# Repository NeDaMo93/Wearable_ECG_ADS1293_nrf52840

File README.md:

# Wearable_ECG_ADS1293_nrf52840
Software for a Functional Demonstrator of a Medical Wearable for ECG and Activity Monitoring with Wireless Communication. With ADS1293, nrf52840, LSM6DSO. Includes an Android App and Python GUI.
# Summary of the research project
This research project aims to design and develop a functional demonstrator of a portable device for long-term Electrocardiogram (ECG) measurements. The proposed device intends to address the need for continuous and non-invasive monitoring of cardiac activity over extended periods, providing valuable insights into the diagnosis and management of cardiovascular conditions.
In addition to enabling long-term Electrocardiogram (ECG) measurements, the developed wearable device will also incorporate advanced sensors to monitor body position, physical activity, and body temperature continuously. This comprehensive approach aims to provide a holistic assessment of the user's physiological status, allowing for a more thorough evaluation of their overall health. 
The primary objective of this project is to create a working prototype that can serve as a foundation for future advancements in the field. The successful development of this device will facilitate subsequent research projects, fostering innovation and further exploration of long-term ECG monitoring technologies at our institution.
Throughout the research process, various aspects, such as hardware design, signal processing algorithms, power efficiency, and user-friendliness, will be carefully considered and optimized to ensure the device's reliability and practicality. Additionally, emphasis will be placed on achieving a cost-effective solution without compromising the quality of data collected.
Ultimately, the successful completion of this project will lay the groundwork for subsequent investigations, encouraging a continuous cycle of research and development in the domain of portable long-term ECG monitoring. The findings and insights gained from this study will contribute significantly to the improvement of cardiac healthcare and enhance the quality of life for individuals with cardiovascular conditions.
# Hardware Architecture
Based on the requirements, the concept architecture and associated functions could be defined by using specific hardware, which is shown in the following figure. For the demonstrator, Nordic's nRF52840 microcontroller acts as the central element, which is available in the form of a developer board from Adafruit Feather. This board has several integrated functions, including push buttons for triggering external events, LEDs for status indication, and an energy-efficient Bluetooth module. A matching SD card module from Adafruit allows local storage of recorded data. The ADS1293 is used as the analog front end for processing ECG signals. The user's activity level and body position are detected with the help of the ST LSM6DSO IMU. Body temperature is measured by using a PT1000 sensor. The Easypack S rechargeable battery system from Varta supplies the necessary energy. Finally, the collected data is transmitted via Bluetooth to a PC and Android smartphone and displayed.

# Software Architecture
The firmware is designed to efficiently handle data acquisition from the ECG and IMU (Inertial Measurement Unit) sensors and transmit the collected data via Bluetooth Low Energy (BLE) while storing it on an SD card. The architecture is implemented using six components, including four separate threads and two interrupt Service Routines (ISRs).

# User Interfaces
## Anrdoid App
The Android application was constructed using the open-source code provided by Nordic for the Android-nRF-Blinky application. 
The Android-nRF-Blinky application, written in Kotlin, serves as an excellent introduction for developers unfamiliar with Bluetooth Low Energy (BLE) and can serve as a template for other projects.
The application uses the Android BLE Library to manage its Bluetooth connections. When the application starts, it scans for nearby BLE devices. Once a device is selected, the application connects to it and discovers its services and characteristics (using the GATT protocol). 

## Python GUI
The Python-based graphical user interface (GUI) connects the ECG device via Bluetooth Low Energy (BLE) and visualizes real-time ECG data. It also displays the patient's activity level, body temperature, heart rate and body posture. The code utilizes PyQt5 for GUI development, Matplotlib for plotting, asyncio for asynchronous tasks, Bleak for BLE communication, and biosppy for ECG signal processing.

# LBS Files
lbs.h and lbs.c must be replaced in your zephyr directory <br>
**lbs.h:**<br>
..\nrf\include\bluetooth\services<br>
**lbs.c:**<br>
..\nrf\subsys\bluetooth\services<br>

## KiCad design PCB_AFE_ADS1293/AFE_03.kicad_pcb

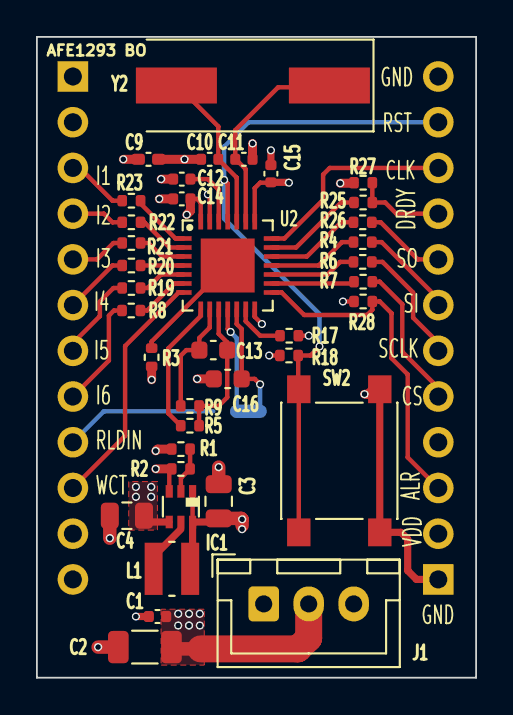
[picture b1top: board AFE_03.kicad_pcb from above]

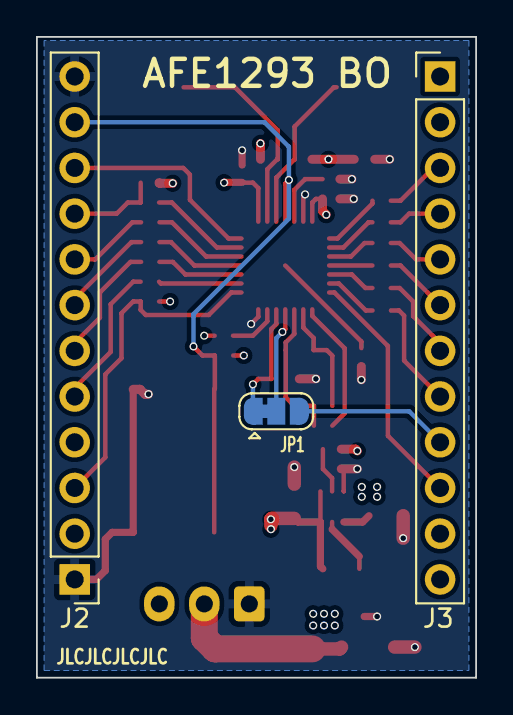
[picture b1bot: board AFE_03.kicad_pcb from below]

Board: 4 copper layers, 24.4 x 35.6 mm, 41 parts (3 on the bottom side), 41 nets.

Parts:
C1, C12, C14, C15: 0.1uF; C_0402_1005Metric
C2: 47uF; C_1206_3216Metric
C3, C4: 10uF; C_0805_2012Metric
C9: 0.1uF; C_0402_1005Metric_Pad0.74x0.62mm_HandSolder
C10, C11: 22pF; C_0402_1005Metric
C13: 1nF; C_0603_1608Metric
C16: 0.1uF; C_0603_1608Metric
IC1: TPS61222DCK; DCK_R-PDSO-G6
J1: Conn_01x03_Socket; JST_XH_B3B-XH-A_1x03_P2.50mm_Vertical
J2, J3: Conn_01x12; PinHeader_1x12_P2.54mm_Vertical
JP1: SolderJumper_3_Open; SolderJumper-3_P1.3mm_Open_RoundedPad1.0x1.5mm
L1: EPL3015-472MLB; IND_EPL3015-472MLB
R1, R17, R18, R27, R28: 1.0M; R_0402_1005Metric
R2: 200k; R_0402_1005Metric
R3, R8, R19, R20, R21, R22, R23: 0; R_0402_1005Metric
R4, R6, R7, R25, R26: 51; R_0402_1005Metric
R5: 10k; R_0402_1005Metric
R9: 10M; R_0402_1005Metric
SW2: SW_SPST; SW_Push_1P1T_NO_6x6mm_H9.5mm
U2: ADS1293CISQ/NOPB; QFN50P500X500X80-29N
Y2: Crystal_Small; Crystal_SMD_HC49-SD

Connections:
ALARMB: J2.3, R28.1, U2.15 (ALARMB)
CLK: J2.10, U2.21 (CLK)
CMOUT: R5.1, U2.8 (CMOUT)
CS: J2.5, R7.2
DRDYB: J2.9, R25.2, R27.1
GND: C1.2, C2.2, C3.2, C4.2, C9.2, C12.2, C14.2, C15.2, C16.2, IC1.3 (GND), J1.1, J2.1, J2.12, R2.2, R3.1, SW2.1 (A), U2.14 (VSSIO), U2.27 (VSS)
IN1: J3.3, R23.1
IN2: J3.4, R22.1
IN3: J3.5, R21.1
IN4: J3.6, R20.1
IN5: J3.7, R19.1
IN6: J3.8, R8.1
MISO: J2.8, R26.2
MOSI: J2.7, R4.2
unnamed: IC1.2 (FB), R1.2, R2.1
unnamed: IC1.5 (L), L1.1
unnamed: C16.1, JP1.1 (A), JP1.2 (C), U2.11 (RLDIN), U2.12 (RLDREF)
unnamed: R7.1, U2.16 (CSB)
unnamed: C12.1, U2.26 (CVREF)
unnamed: R3.2, U2.29 (DAP)
unnamed: R25.1, U2.20 (DRDYB)
unnamed: R23.2, U2.1 (IN1)
unnamed: R22.2, U2.2 (IN2)
unnamed: R21.2, U2.3 (IN3)
unnamed: R20.2, U2.4 (IN4)
unnamed: R19.2, U2.5 (IN5)
unnamed: R8.2, U2.6 (IN6)
unnamed: R6.1, U2.17 (SCLK)
unnamed: R4.1, U2.18 (SDI)
unnamed: R26.1, U2.19 (SDO)
unnamed: R17.2, U2.13 (SYNCB)
unnamed: C11.2, U2.23 (XTAL1), Y2.1
unnamed: C10.2, U2.24 (XTAL2), Y2.2
RLDIN: J3.9, JP1.3 (B)
RLDINIV: C13.2, R5.2, R9.2, U2.10 (RLDINV)
RLDOUT: C13.1, R9.1, U2.9 (RLDOUT)
RSTB: J2.11, R18.2, SW2.2 (B), U2.25 (RSTB)
SCLK: J2.6, R6.2
VDD: C1.1, C2.1, C3.1, C15.1, IC1.1 (VIN), IC1.6 (EN), J1.2, J2.2, L1.2, R17.1, R18.1, R27.2, R28.2, U2.22 (VDDIO)
VDDA: C4.1, C9.1, C10.1, C11.1, C14.1, IC1.4 (VOUT), R1.1, U2.28 (VDD)
WCT: J3.10, U2.7 (WCT)

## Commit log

2023-06-11 initital commit
2023-08-15 added gitignore
2023-08-15 added battery management
2023-08-15 minor fix
2023-08-15 change color of GUI
2023-08-15 Added PCB files
